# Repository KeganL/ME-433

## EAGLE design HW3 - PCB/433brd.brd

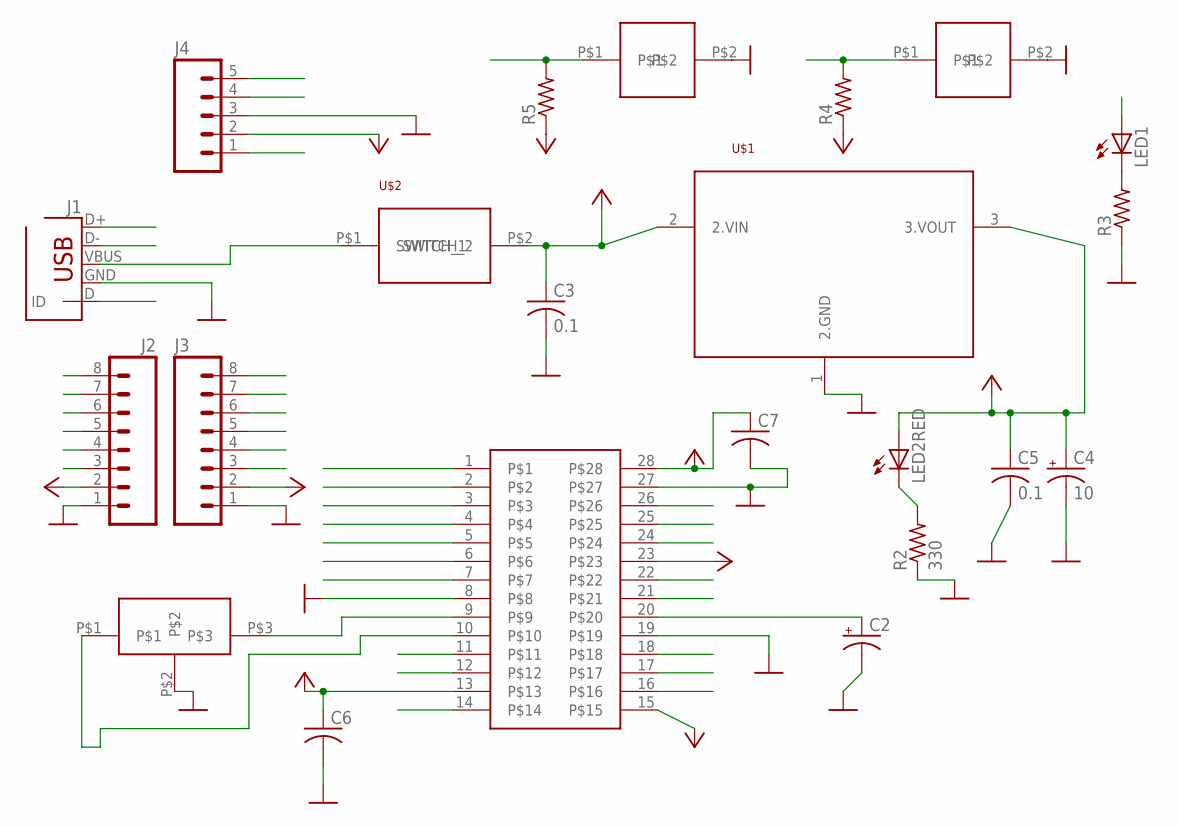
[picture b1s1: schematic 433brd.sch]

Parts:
C2: CPOL-USE1.8-4; E1,8-4
C3, C5: 0.1; C025-024X044
C4: 10; E1,8-4
C6, C7: C-US025-024X044; C025-024X044
J1: USB-MB-H
J2, J3: M08; 1X08_ROUND
J4: M05PTH; 1X05
LED1, LED2RED: LED3MM
R2: 330; 0204/7
R3, R4, R5: R-US_0204/7; 0204/7
U$1: MCP1702; TO92
U$2: SLIDE_SWITCH
U$3: RESONATOR
U$4: DIPMOUNT; DIL28-3
U$5, U$6: PUSHBUTTON

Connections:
+3V3: C4.+, C5.1, C6.1, C7.1, J2.2, J4.2, LED2RED.A, R4.1, R5.1, U$1.3 (3.VOUT), U$4.13, U$4.23, U$4.28
A0: J2.8, U$4.2
A1: J2.7, U$4.3
A4/LED: J2.3, LED1.A, U$4.12
B2: J2.6, U$4.6
B3: J2.5, U$4.7
B4/USER: J2.4, R5.2, U$4.11, U$5.P$1
B7: J3.3, U$4.16
B8: J3.4, U$4.17
B9: J3.5, U$4.18
B13: J3.6, U$4.24
B14: J3.7, U$4.25
B15: J3.8, U$4.26
D+: J1.D+, U$4.21
D-: J1.D-, U$4.22
GND: C2.-, C3.2, C4.-, C5.2, C6.2, C7.2, J1.GND, J2.1, J3.1, J4.3, R2.1, R3.1, U$1.1 (2.GND), U$3.P$2, U$4.8, U$4.19, U$4.27, U$5.P$2, U$6.P$2
MCLR: J4.1, R4.2, U$4.1, U$6.P$1
unnamed: U$3.P$3, U$4.9
unnamed: LED2RED.K (C), R2.2
unnamed: U$3.P$1, U$4.10
unnamed: LED1.K (C), R3.2
unnamed: C2.+, U$4.20
PGC: J4.5, U$4.5
PGD: J4.4, U$4.4
USBID: J1.ID, U$4.14
VBUS: J1.VBUS, U$2.P$1 (SWITCH_1)

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
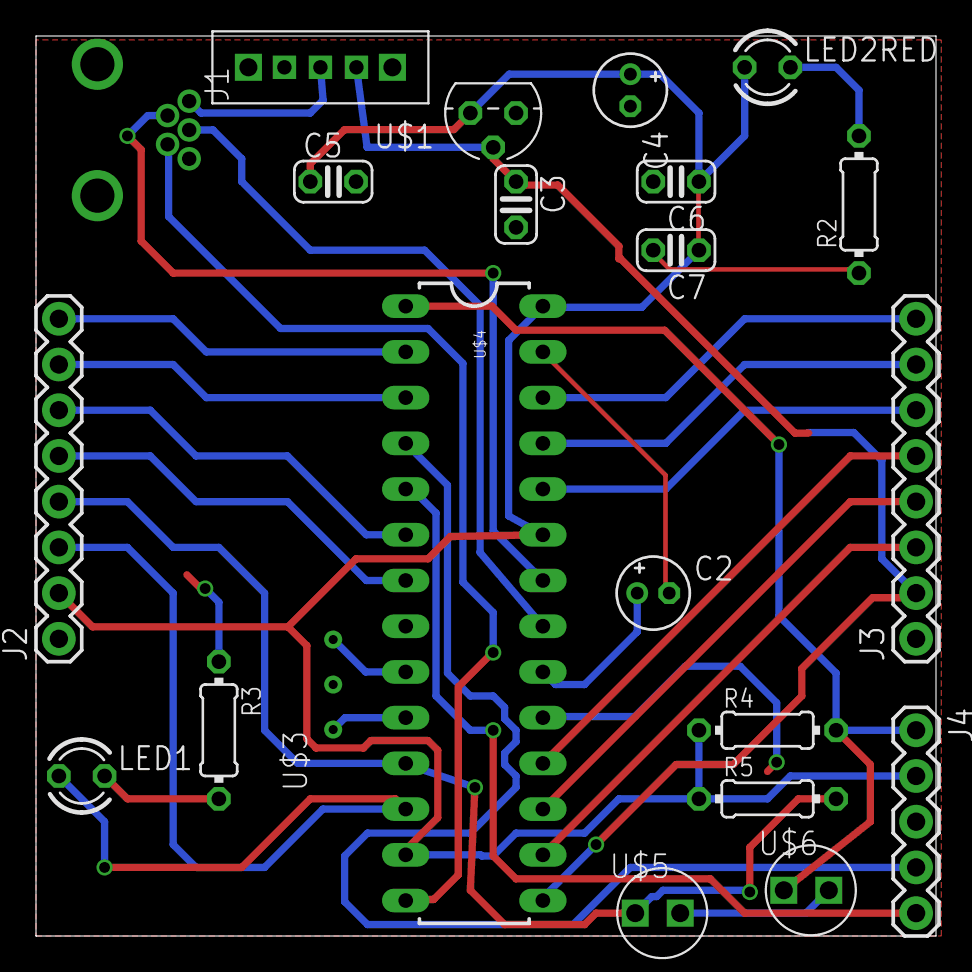
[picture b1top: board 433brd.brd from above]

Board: 2 copper layers, 50.0 x 50.0 mm, 22 parts (0 on the bottom side), 28 nets.

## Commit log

2016-04-13 In Progress
2016-04-14 Ready for checking
2016-05-05 SPI works, I2C in progress
2016-05-05 Cleaned up failed i2c files in SPI folder
    Will update with i2c in its own folder
2016-05-05 I2C and SPI working separately
2016-05-05 (cleaned up again)
2016-06-09 HW 1-4, 8, 12
    Missing: IMU, LCD, Mouse; laser cut box; Android: HelloWorld, CDC app,
    Tech cup combo app, racer code
2016-06-09 1-4, 8-10, 12
    Still needs IMU, LCD, Mouse, Box; CDC android, tech cup combo app, and
    racer code
2016-06-09 1-4, 8-10, 12-13 complete
    Needs IMU, LCD, Mouse; Tech Cup Android app, Pic racer code, box
2016-06-09 HW6 partly working
    1-4, 8-10, 12-13 finished
    6 in progress
    5, 7, 11, 14, 15 to do
2016-06-10 1-4, 6*, 8-10, 11*, 12-13, 14*
    * some issues
2016-06-10 1-4, 5*, 6*, 8-10, 11*, 12-13, 14*
    *some issues
    Remainder of 5 is dependent upon 6, which I have yet to get working
    fully.
2016-06-10 1-4, 5*, 6, 8-10, 11*, 12-13, 14*
    *still has problems
2016-06-10 1-6, 8-10, 11*, 12-13, 14*
    * has problems
